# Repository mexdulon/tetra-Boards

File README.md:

View this project on [CADLAB.io](https://cadlab.io/node/872). 

# tetra-Boards
## mexdulon Modules for Experiments with Digital Electronics

This repository includes material like schematics, layouts, instructions and explanations for mexdulon tetra-Boards. 
The modular system is developed for understanding digital electronics by experimenting. Next to the standard digital components (gates, counter, register, etc.) we created also boards for analog signals and external outputs (motor driver, relay, power FET). All these published boards are licenced as Open Hardware, see below.
If you have any suggestions, modifications or extensions, please feel free to share it with us.

## List with all boards

|Code|Description                       |
|----|----------------------------------|
|7SD |7-Segment Display                 |
|ADA |Adapter 2x5 Port                  |
|ADC |Analog Digital Converter          |
|ADD |Adder 2x4 Bit                     |
|ALU |Arithmetic Logic Unit             |
|AMU |Analog Multiplexer 2x4:1          |
|AND |AND & NAND 4x2:1                  |
|ANS |Arduino Nano Shield with Display  |
|ARD |Arduino Shield (Uno, Leonardo)    |
|B7D |BCD 7-Segment Decoder             |
|BCC |BCD Up/Down Counter               |
|BNC |Binary Up/Down Counter 4 Bit      |
|BTN |Quad Buttons                      |
|C12 |Counter 12bit                     |
|CDL |Counter Divider Logic             |
|CLK |Clock Generator                   |
|CMP |Comparator 2x4 Bit                |
|CNT |Dual Counter 4 Bit                |
|D12 |Demultiplexer 1:2                 |
|D14 |Demultiplexer 1:4                 |
|D18 |Demultiplexer 1:8                 |
|DAC |Digital Analog Converter (DAC)    |
|DEC |Decoder 1:8                       |
|DFF |Dual D Flip-flop                  |
|DIP |DIP Socket                        |
|DMD |Dot Matrix Display 4x4            |
|DMX |Diode Matrix 4x4                  |
|ENC |Encoder 8:3                       | 
|FET |Quad Power FET                    |   
|INV |Dual Inverter (NOT)               |     
|IOP |Dual IO Port                      | 
|JAD |Jumper Adapter                    |   
|JKF |JK Flip-flop 2x                   |    
|JMP |Jumper 2x4                        |
|JOY |Joystick with Button              |
|KEY |Keyboard 4x4                      | 
|LAD |Line Adapter                      | 
|LED |Dual LED Display                  |
|M81 |Multiplexer 8:1                   |
|MTR |Dual Motor Shield                 |
|MUX |Multiplexer 2:1                   |
|MXC |Modulo X Counter (3/6/9/12)       | 
|N33 |Tripple NAND 3:1                  |
|NOR |OR & NOR 4x2:1                    |
|OPA |Operational Amplifier             |
|PAN |Dual Port AND 4:1                 |
|PIN |Pin Header                        |
|POR |Dual Port OR 4:1                  |
|PRG |Pseudo Random Generator           |
|PWM |PWM Generator                     |
|PXO |Dual Port XOR 4:1                 |
|QRS |Quad RS Buttons                   |
|REG |Register 2x4                      |
|RGB |RGB LED & Buzzer                  |
|RGF |Register File 4x4                 |
|RLY |Quad Relay                        |
|ROM |ROM Diodes 4x4                    |
|RSG |RS Generator                      |
|SAD |Shift Adapter                     |
|SOC |Quad Socket                       |
|SRC |SRAM Cell                         |
|SRG |Shift Register                    |
|SWG |Square Wave Generator             |
|SWI |Quad Switch                       |
|TMP |Temperature Sensor                |
|UNI |Universal Register                |
|WNG |White Noise Generator             |
|XOR |XOR & XNOR 4x2:1                  |

# Copyright and License
Copyright Oliver Krebs 2017.

This documentation describes Open Hardware and is licensed under the CERN OHL v. 1.2. 

You may redistribute and modify this documentation under the terms of the CERN OHL v.1.2. (http://ohwr.org/cernohl). This documentation is distributed WITHOUT ANY EXPRESS OR IMPLIED WARRANTY, INCLUDING OF MERCHANTABILITY, SATISFACTORY QUALITY AND FITNESS FOR A PARTICULAR PURPOSE. Please see the CERN OHL v.1.2 for applicable conditions

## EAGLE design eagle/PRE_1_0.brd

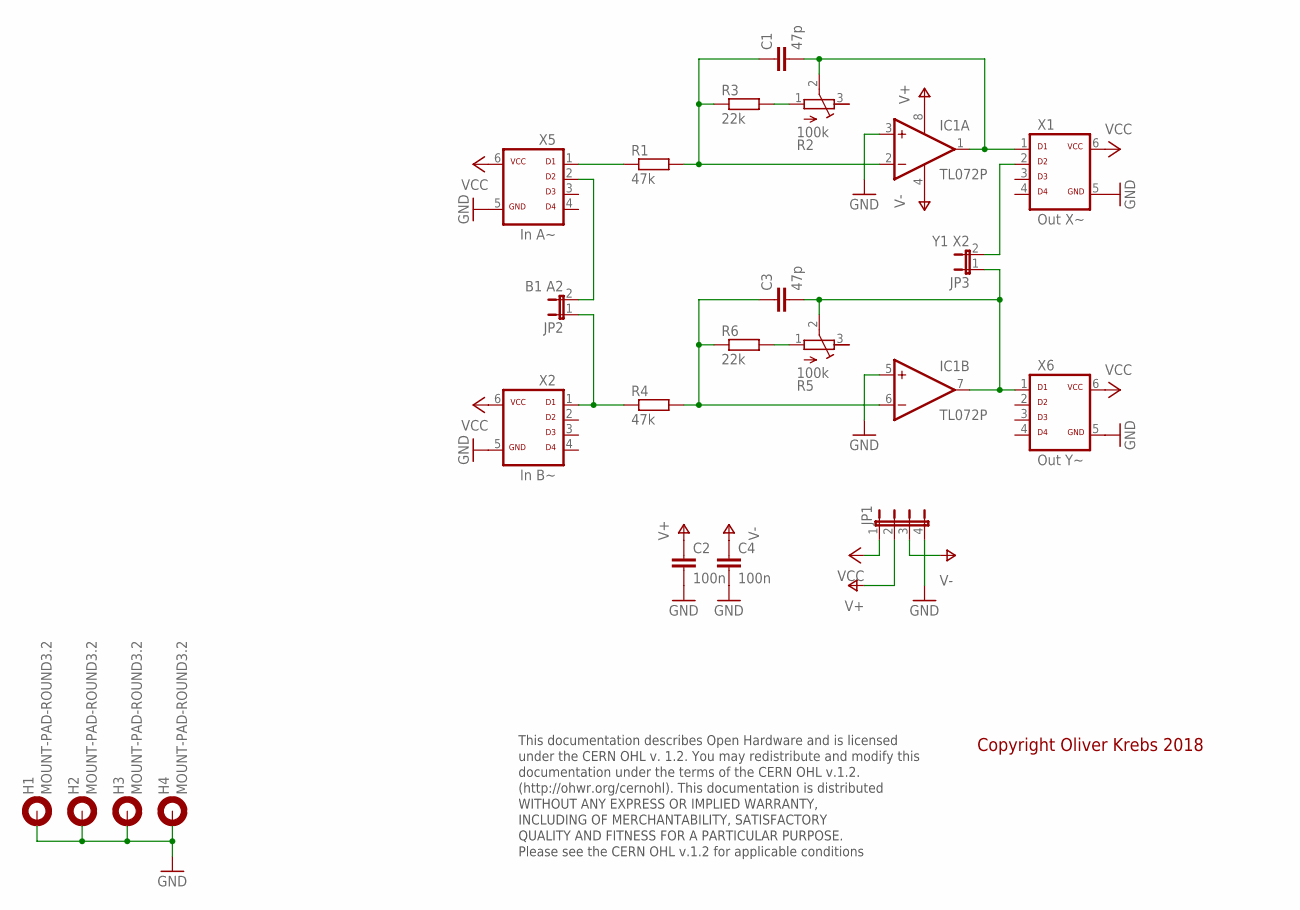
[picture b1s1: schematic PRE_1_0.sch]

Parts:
C1, C3: 47p; C050-025X075
C2, C4: 100n; C050-025X075
H1, H2, H3, H4: MOUNT-PAD-ROUND3.2; 3,2-PAD
IC1: TL072P; DIL08
JP1: JP4E; JP4
JP2: B1 A2; JP1
JP3: Y1 X2; JP1
R1, R4: 47k; 0207/10
R2, R5: 100k; ACP-6L
R3, R6: 22k; 0207/10
X1: Out X~; ML-6
X2: In B~; ML-6
X5: In A~; ML-6
X6: Out Y~; ML-6

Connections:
GND: C2.2, C4.2, H1.B3,2, H2.B3,2, H3.B3,2, H4.B3,2, IC1.3 (+IN), IC1.5 (+IN), JP1.4, X1.5, X2.5, X5.5, X6.5
unnamed: JP3.2, X1.2
unnamed: R5.1 (A), R6.2
unnamed: C1.2, IC1.1 (OUT), R2.2 (S), X1.1
unnamed: C3.2, IC1.7 (OUT), JP3.1, R5.2 (S), X6.1
unnamed: C1.1, IC1.2 (-IN), R1.2, R3.1
unnamed: JP2.2, X5.2
unnamed: R2.1 (A), R3.2
unnamed: C3.1, IC1.6 (-IN), R4.2, R6.1
unnamed: JP2.1, R4.1, X2.1
unnamed: R1.1, X5.1
V+: C2.1, IC1.8 (V+), JP1.2
V-: C4.1, IC1.4 (V-), JP1.3
VCC: JP1.1, X1.6, X2.6, X5.6, X6.6

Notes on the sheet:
This documentation describes Open Hardware and is licensed under the CERN OHL v. 1.2. You may redistribute and modify this documentation under the terms of the CERN OHL v.1.2. (http://ohwr.org/cernohl). This documentation is distributed WITHOUT ANY EXPRESS OR IMPLIED WARRANTY, INCLUDING OF MERCHANT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
Copyright Oliver Krebs 2018

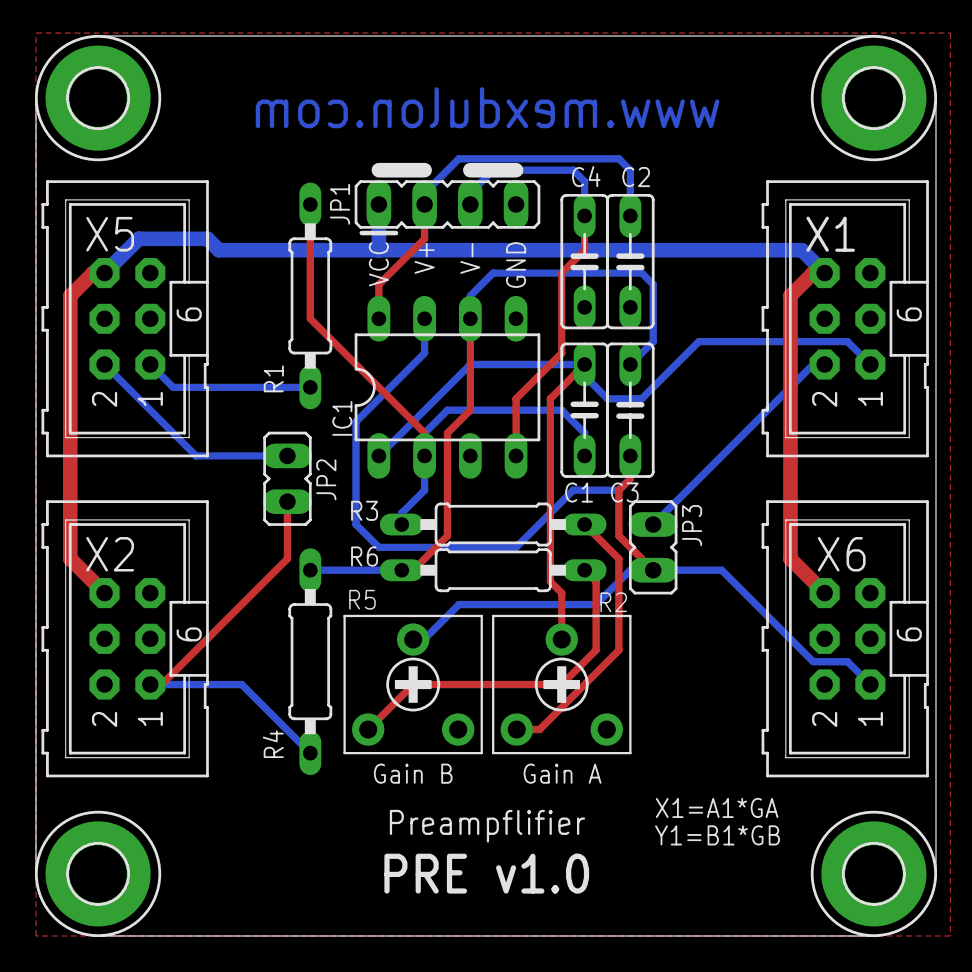
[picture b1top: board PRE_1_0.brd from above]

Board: 2 copper layers, 50.0 x 50.0 mm, 22 parts (0 on the bottom side), 14 nets.

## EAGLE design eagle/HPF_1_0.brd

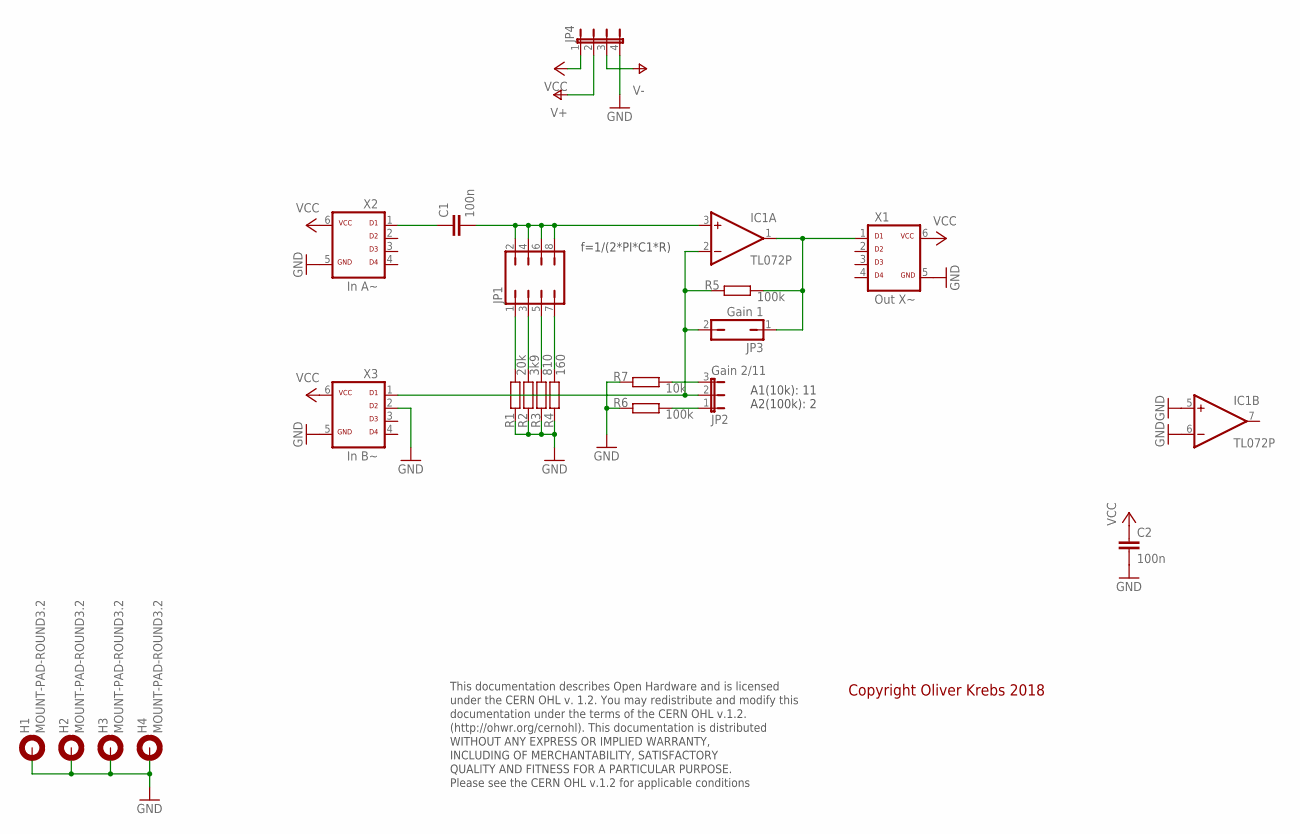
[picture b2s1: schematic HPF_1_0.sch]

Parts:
C1, C2: 100n; C050-025X075
H1, H2, H3, H4: MOUNT-PAD-ROUND3.2; 3,2-PAD
IC1: TL072P; DIL08
JP1: JP4Q
JP2: Gain 2/11; JP2-U
JP3: Gain 1; JP1
JP4: JP4E; JP4
R1: 20k; 0207/10
R2: 3k9; 0207/10
R3: 810; 0207/10
R4: 160; 0207/10
R5, R6: 100k; 0207/10
R7: 10k; 0207/10
X1: Out X~; ML-6
X2: In A~; ML-6
X3: In B~; ML-6

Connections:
GND: C2.2, H1.B3,2, H2.B3,2, H3.B3,2, H4.B3,2, IC1.5 (+IN), IC1.6 (-IN), JP4.4, R1.1, R2.1, R3.1, R4.1, R6.1, R7.1, X1.5, X2.5, X3.2, X3.5
unnamed: JP1.1, R1.2
unnamed: JP1.3, R2.2
unnamed: JP1.5, R3.2
unnamed: JP1.7, R4.2
unnamed: IC1.2 (-IN), JP2.2, JP3.2, R5.1, X3.1
unnamed: C1.2, IC1.3 (+IN), JP1.2, JP1.4, JP1.6, JP1.8
unnamed: C1.1, X2.1
unnamed: IC1.1 (OUT), JP3.1, R5.2, X1.1
unnamed: JP2.3, R7.2
unnamed: JP2.1, R6.2
V+: IC1.8 (V+), JP4.2
V-: IC1.4 (V-), JP4.3
VCC: C2.1, JP4.1, X1.6, X2.6, X3.6

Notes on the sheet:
This documentation describes Open Hardware and is licensed under the CERN OHL v. 1.2. You may redistribute and modify this documentation under the terms of the CERN OHL v.1.2. (http://ohwr.org/cernohl). This documentation is distributed WITHOUT ANY EXPRESS OR IMPLIED WARRANTY, INCLUDING OF MERCHANT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
Copyright Oliver Krebs 2018
A1(10k): 11 A2(100k): 2
f=1/(2*PI*C1*R)

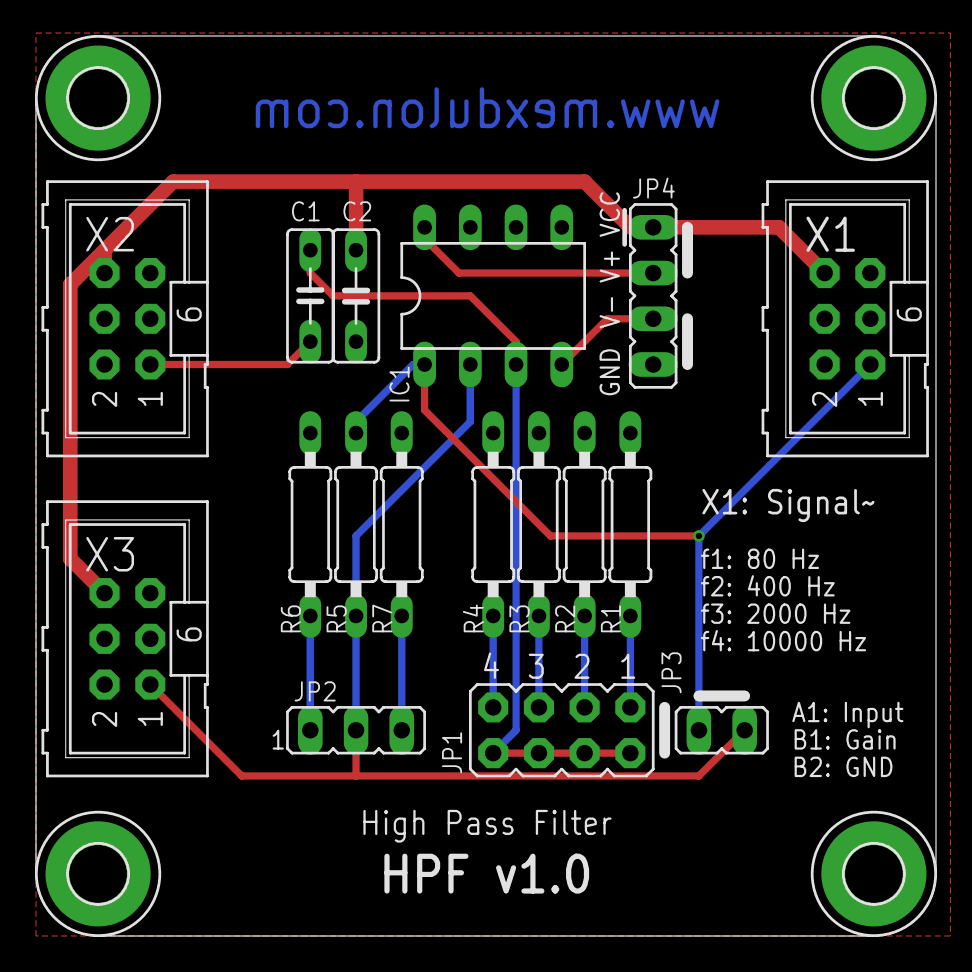
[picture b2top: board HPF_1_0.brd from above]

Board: 2 copper layers, 50.0 x 50.0 mm, 21 parts (0 on the bottom side), 14 nets.

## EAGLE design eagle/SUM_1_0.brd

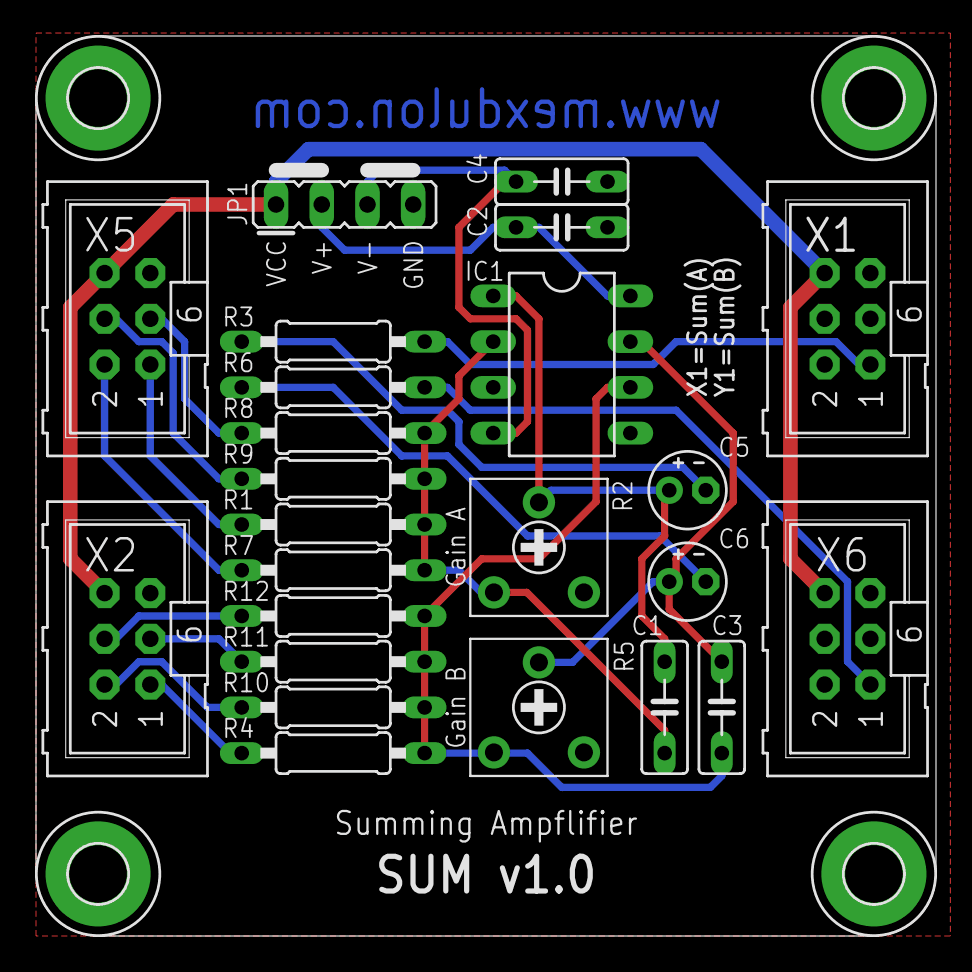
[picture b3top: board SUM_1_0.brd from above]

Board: 2 copper layers, 50.0 x 50.0 mm, 28 parts (0 on the bottom side), 20 nets.

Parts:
C1, C3: 22p; C050-025X075
C2, C4: 100n; C050-025X075
C5, C6: 4u7; E2-4
H1, H2, H3, H4: MOUNT-PAD-ROUND3.2; 3,2-PAD
IC1: TL072P; DIL08
JP1: JP4
R1, R4, R7, R8, R9, R10, R11, R12: 22k; 0207/10
R2, R5: 25k; ACP-6L
R3, R6: 47; 0207/10
X1: X~; ML-6
X2: B~; ML-6
X5: A~; ML-6
X6: Y~; ML-6

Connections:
GND: C2.2, C4.2, H1.B3,2, H2.B3,2, H3.B3,2, H4.B3,2, IC1.3, IC1.5, JP1.4, X1.5, X2.5, X5.5, X6.5
unnamed: C5.-, R3.1
unnamed: R3.2, X1.1
unnamed: C1.2, C5.+, IC1.1, R2.2
unnamed: C3.2, C6.+, IC1.7, R5.2
unnamed: C1.1, IC1.2, R1.2, R2.1, R7.2, R8.2, R9.2
unnamed: R7.1, X5.2
unnamed: C3.1, IC1.6, R4.2, R5.1, R10.2, R11.2, R12.2
unnamed: C6.-, R6.1
unnamed: R4.1, X2.1
unnamed: R1.1, X5.1
unnamed: R8.1, X5.3
unnamed: R9.1, X5.4
unnamed: R6.2, X6.1
unnamed: R10.1, X2.2
unnamed: R11.1, X2.3
unnamed: R12.1, X2.4
V+: C2.1, IC1.8, JP1.2
V-: C4.1, IC1.4, JP1.3
VCC: JP1.1, X1.6, X2.6, X5.6, X6.6

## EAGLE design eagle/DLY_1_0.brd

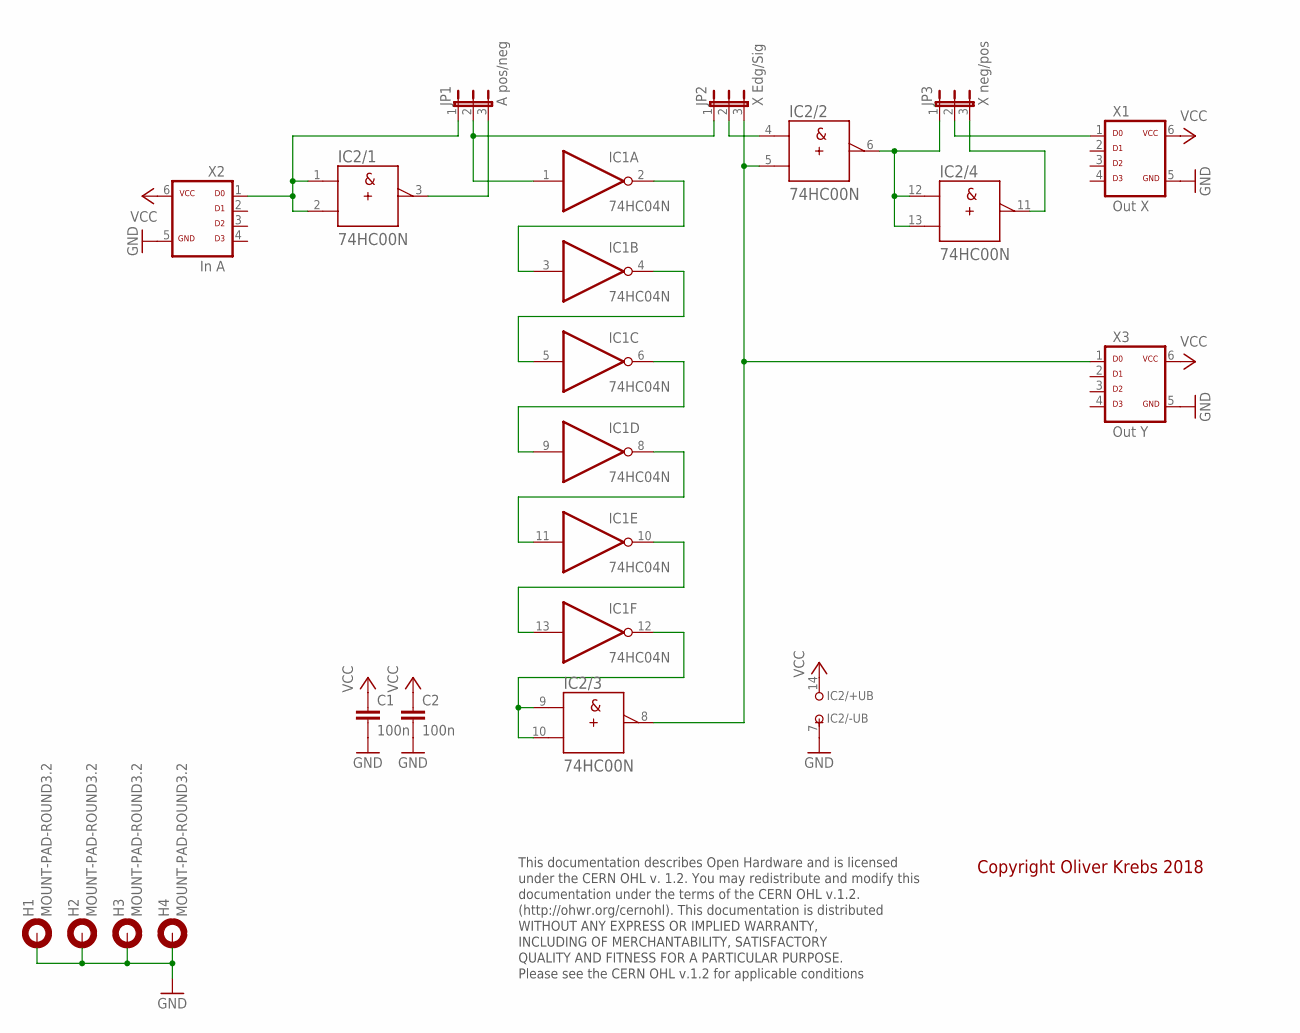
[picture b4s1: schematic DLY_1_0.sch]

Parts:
C1, C2: 100n; C050-025X075
H1, H2, H3, H4: MOUNT-PAD-ROUND3.2; 3,2-PAD
IC1: 74HC04N; DIL14
IC2: 74HC00N; DIL14
JP1: A pos/neg; JP2
JP2: X Edg/Sig; JP2
JP3: X neg/pos; JP2
X1: Out X; ML-6
X2: In A; ML-6
X3: Out Y; ML-6

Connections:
GND: C1.2, C2.2, H1.B3,2, H2.B3,2, H3.B3,2, H4.B3,2, IC1.7 (GND), IC2.7 (-UB), X1.5, X2.5, X3.5
unnamed: IC2.1 (A), IC2.2 (B), JP1.1, X2.1
unnamed: IC1.2 (O), IC1.3 (I)
unnamed: IC1.4 (O), IC1.5 (I)
unnamed: IC1.6 (O), IC1.9 (I)
unnamed: IC1.8 (O), IC1.11 (I)
unnamed: IC2.5 (B), IC2.8 (Y), JP2.3, X3.1
unnamed: IC2.3 (Y), JP1.3
unnamed: IC1.1 (I), JP1.2, JP2.1
unnamed: IC2.4 (A), JP2.2
unnamed: IC1.12 (O), IC2.9 (A), IC2.10 (B)
unnamed: IC2.6 (Y), IC2.12 (A), IC2.13 (B), JP3.1
unnamed: IC2.11 (Y), JP3.3
unnamed: JP3.2, X1.1
unnamed: IC1.10 (O), IC1.13 (I)
VCC: C1.1, C2.1, IC1.14 (VCC), IC2.14 (+UB), X1.6, X2.6, X3.6

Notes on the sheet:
This documentation describes Open Hardware and is licensed under the CERN OHL v. 1.2. You may redistribute and modify this documentation under the terms of the CERN OHL v.1.2. (http://ohwr.org/cernohl). This documentation is distributed WITHOUT ANY EXPRESS OR IMPLIED WARRANTY, INCLUDING OF MERCHANT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
Copyright Oliver Krebs 2018

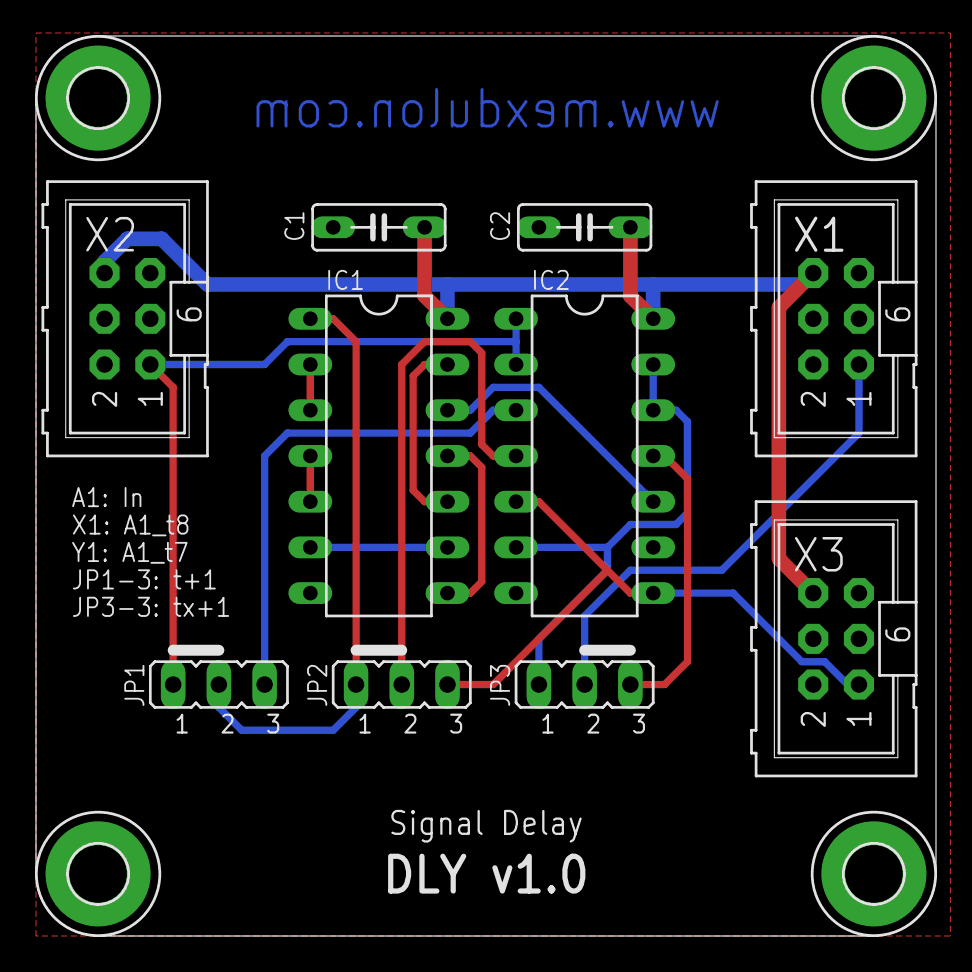
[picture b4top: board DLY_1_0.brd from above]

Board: 2 copper layers, 50.0 x 50.0 mm, 14 parts (0 on the bottom side), 16 nets.

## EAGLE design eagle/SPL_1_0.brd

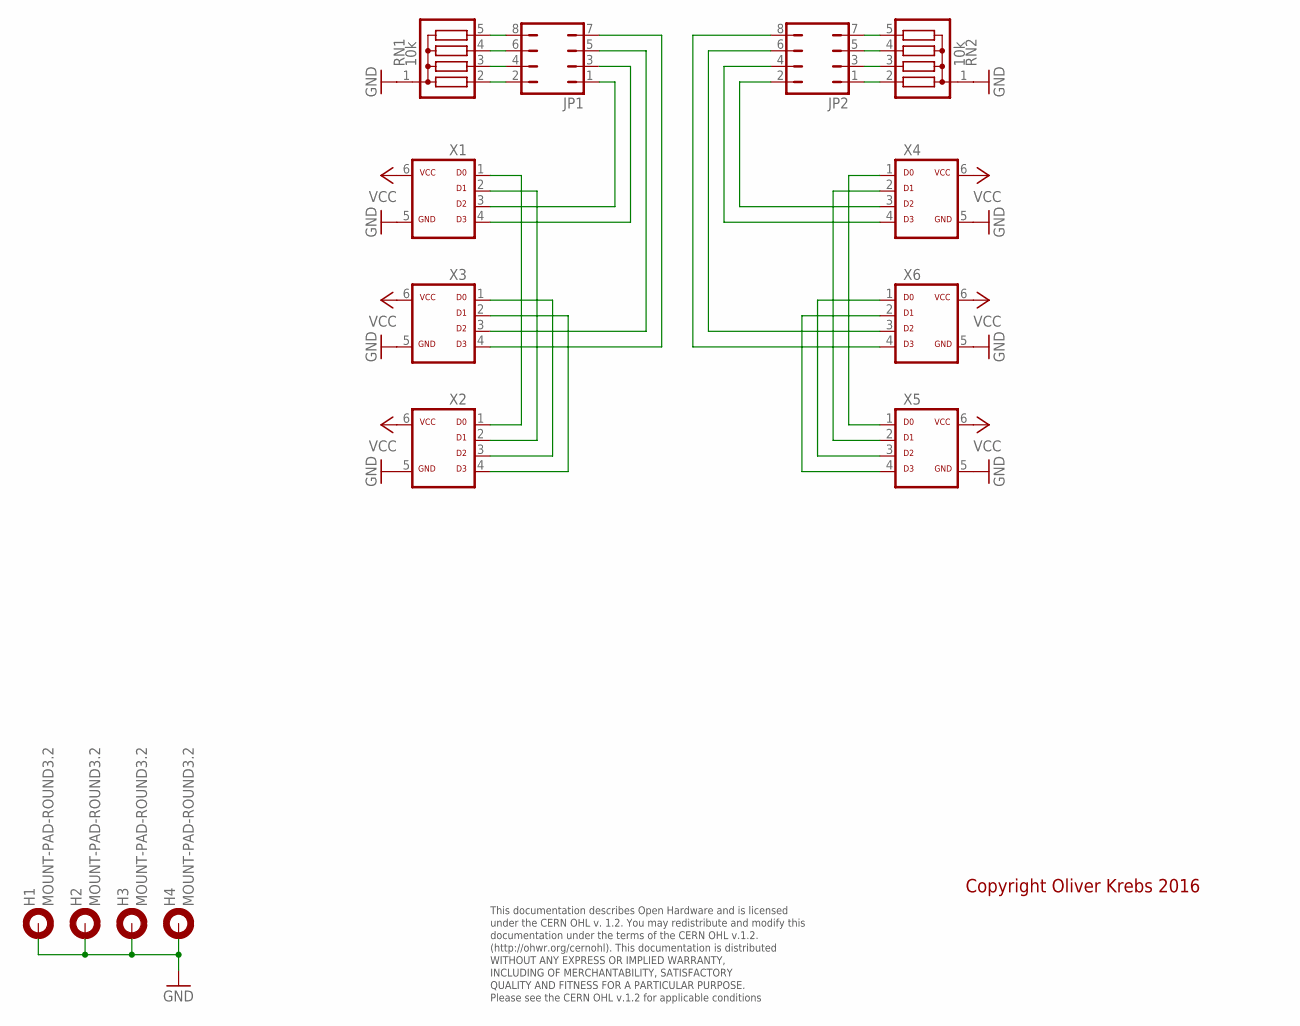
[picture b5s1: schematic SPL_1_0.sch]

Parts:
H1, H2, H3, H4: MOUNT-PAD-ROUND3.2; 3,2-PAD
JP1, JP2: JP4Q
RN1, RN2: 10k; SIL5
X1, X2, X3, X4, X5, X6: ML6D; ML-6

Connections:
GND: H1.B3,2, H2.B3,2, H3.B3,2, H4.B3,2, RN1.1, RN2.1, X1.5, X2.5, X3.5, X4.5, X5.5, X6.5
unnamed: X1.1, X2.1
unnamed: X1.2, X2.2
unnamed: X2.3, X3.1
unnamed: X2.4, X3.2
unnamed: X4.1, X5.1
unnamed: X4.2, X5.2
unnamed: X5.3, X6.1
unnamed: X5.4, X6.2
unnamed: JP1.2, RN1.2
unnamed: JP1.4, RN1.3
unnamed: JP1.6, RN1.4
unnamed: JP1.8, RN1.5
unnamed: JP2.1, RN2.2
unnamed: JP2.3, RN2.3
unnamed: JP2.5, RN2.4
unnamed: JP2.7, RN2.5
unnamed: JP1.1, X1.3
unnamed: JP1.3, X1.4
unnamed: JP1.5, X3.3
unnamed: JP1.7, X3.4
unnamed: JP2.8, X6.4
unnamed: JP2.6, X6.3
unnamed: JP2.4, X4.4
unnamed: JP2.2, X4.3
VCC: X1.6, X2.6, X3.6, X4.6, X5.6, X6.6

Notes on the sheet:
This documentation describes Open Hardware and is licensed under the CERN OHL v. 1.2. You may redistribute and modify this documentation under the terms of the CERN OHL v.1.2. (http://ohwr.org/cernohl). This documentation is distributed WITHOUT ANY EXPRESS OR IMPLIED WARRANTY, INCLUDING OF MERCHANT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
Copyright Oliver Krebs 2016

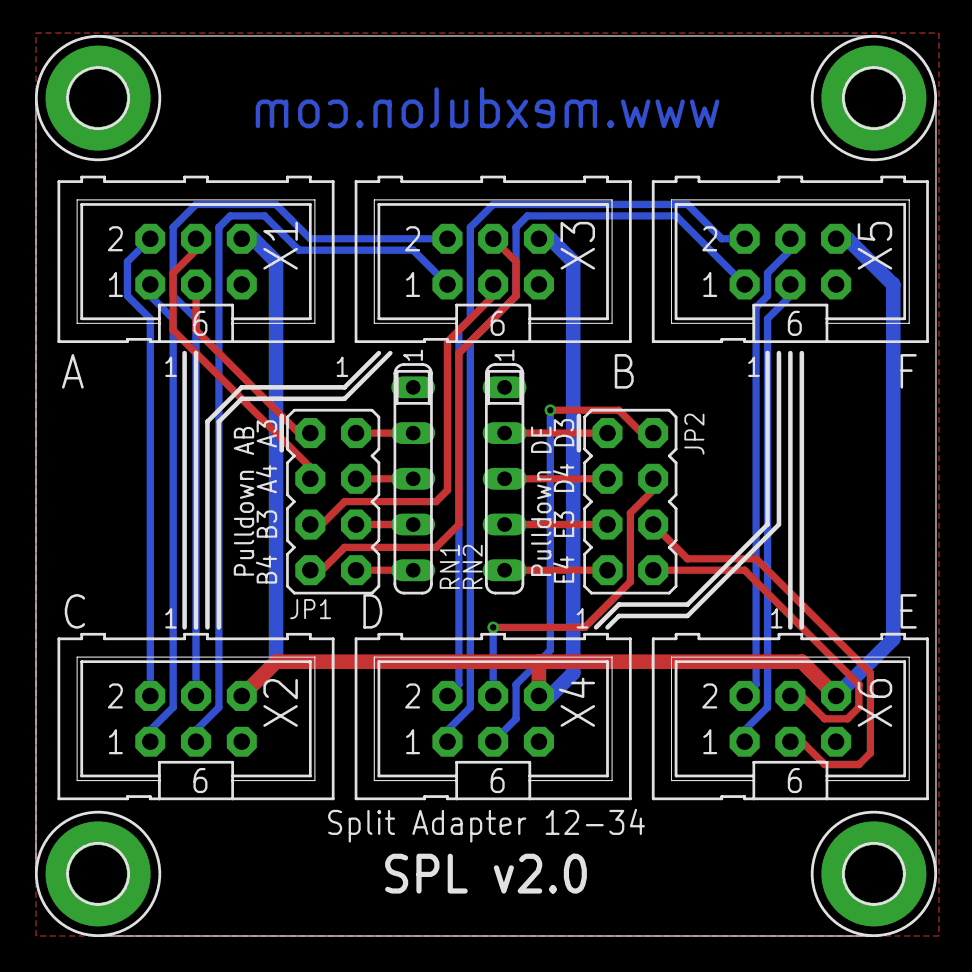
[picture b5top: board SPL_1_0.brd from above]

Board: 2 copper layers, 50.0 x 50.0 mm, 14 parts (0 on the bottom side), 26 nets.

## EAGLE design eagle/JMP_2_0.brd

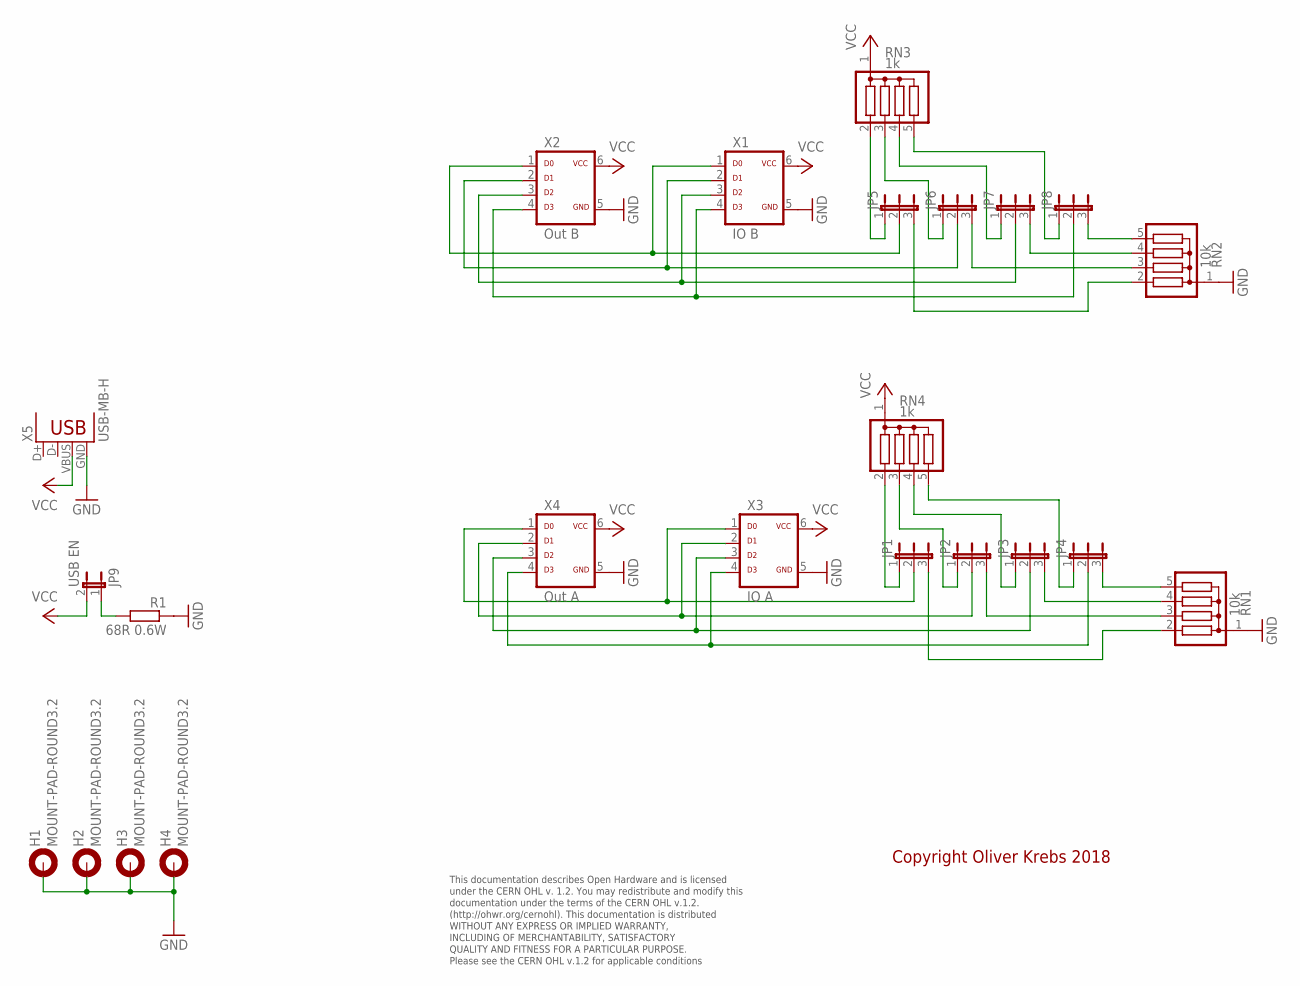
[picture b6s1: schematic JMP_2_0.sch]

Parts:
H1, H2, H3, H4: MOUNT-PAD-ROUND3.2; 3,2-PAD
JP1, JP2, JP3, JP4, JP5, JP6, JP7, JP8: JP2E; JP2-S
JP9: USB EN; JP1
R1: 68R 0.6W; 0207/10
RN1, RN2: 10k; SIL5
RN3, RN4: 1k; SIL5
X1: IO B; ML-6
X2: Out B; ML-6
X3: IO A; ML-6
X4: Out A; ML-6
X5: USB-MB-H

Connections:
GND: H1.B3,2, H2.B3,2, H3.B3,2, H4.B3,2, R1.1, RN1.1, RN2.1, X1.5, X2.5, X3.5, X4.5, X5.GND
unnamed: JP5.2, X1.1, X2.1
unnamed: JP6.2, X1.2, X2.2
unnamed: JP1.2, X3.1, X4.1
unnamed: JP8.2, X1.4, X2.4
unnamed: JP2.2, X3.2, X4.2
unnamed: JP4.2, X3.4, X4.4
unnamed: JP7.2, X1.3, X2.3
unnamed: JP3.2, X3.3, X4.3
unnamed: JP8.1, RN3.5
unnamed: JP9.1, R1.2
unnamed: JP5.1, RN3.2
unnamed: JP6.1, RN3.3
unnamed: JP7.1, RN3.4
unnamed: JP1.1, RN4.2
unnamed: JP2.1, RN4.3
unnamed: JP3.1, RN4.4
unnamed: JP4.1, RN4.5
unnamed: JP5.3, RN2.2
unnamed: JP6.3, RN2.3
unnamed: JP7.3, RN2.4
unnamed: JP8.3, RN2.5
unnamed: JP4.3, RN1.5
unnamed: JP3.3, RN1.4
unnamed: JP2.3, RN1.3
unnamed: JP1.3, RN1.2
VCC: JP9.2, RN3.1, RN4.1, X1.6, X2.6, X3.6, X4.6, X5.VBUS

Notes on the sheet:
This documentation describes Open Hardware and is licensed under the CERN OHL v. 1.2. You may redistribute and modify this documentation under the terms of the CERN OHL v.1.2. (http://ohwr.org/cernohl). This documentation is distributed WITHOUT ANY EXPRESS OR IMPLIED WARRANTY, INCLUDING OF MERCHANT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
Copyright Oliver Krebs 2018

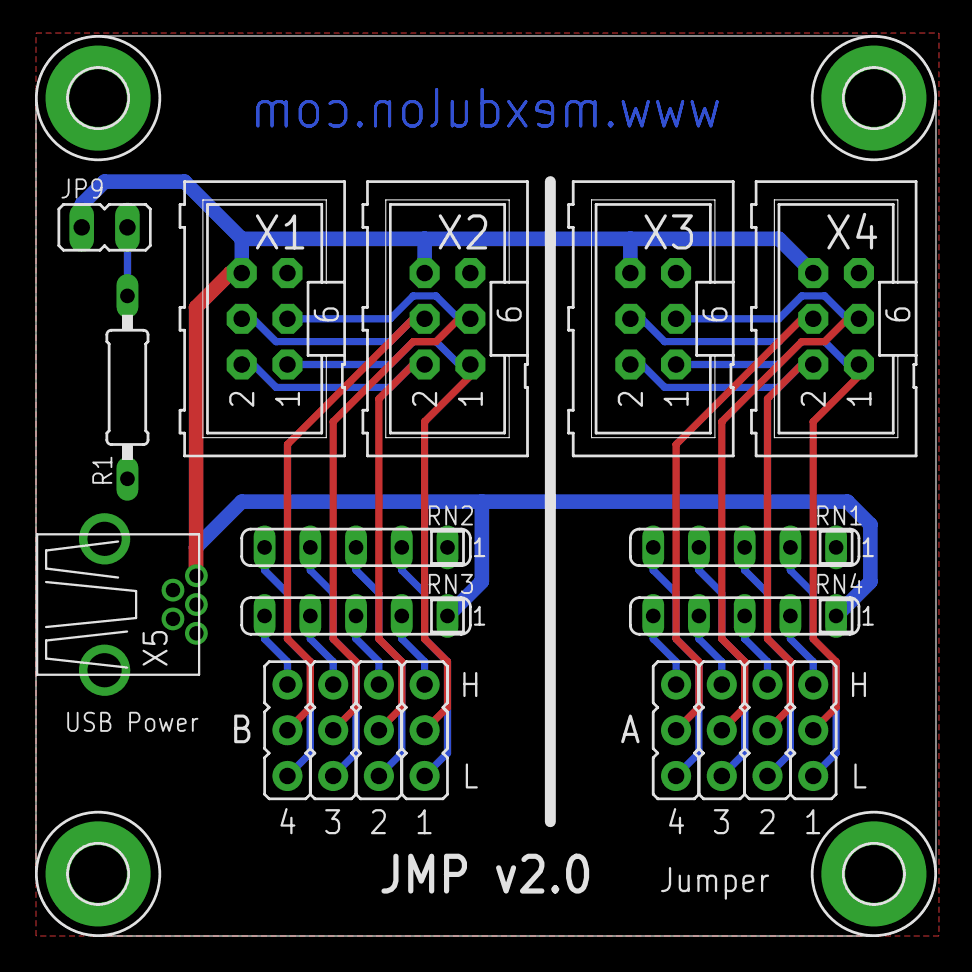
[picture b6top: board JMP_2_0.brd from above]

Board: 2 copper layers, 50.0 x 50.0 mm, 23 parts (0 on the bottom side), 27 nets.

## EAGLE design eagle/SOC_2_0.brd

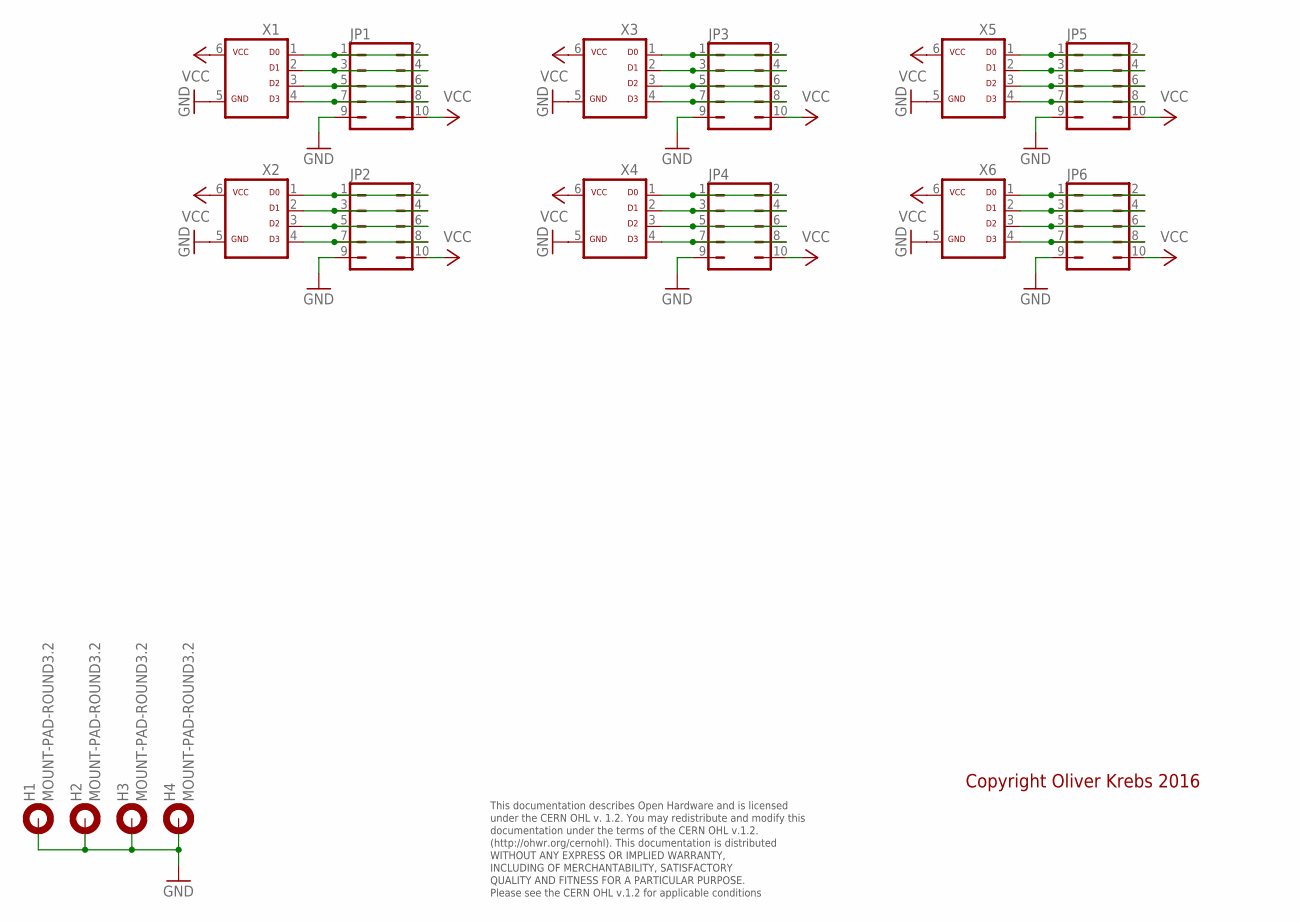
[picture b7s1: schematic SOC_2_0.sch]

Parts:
H1, H2, H3, H4: MOUNT-PAD-ROUND3.2; 3,2-PAD
JP1, JP2, JP3, JP4, JP5, JP6: JP5Q
X1, X2, X3, X4, X5, X6: ML6D; ML-6

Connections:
GND: H1.B3,2, H2.B3,2, H3.B3,2, H4.B3,2, JP1.9, JP2.9, JP3.9, JP4.9, JP5.9, JP6.9, X1.5, X2.5, X3.5, X4.5, X5.5, X6.5
unnamed: JP1.1, JP1.2, X1.1
unnamed: JP1.3, JP1.4, X1.2
unnamed: JP1.5, JP1.6, X1.3
unnamed: JP1.7, JP1.8, X1.4
unnamed: JP2.1, JP2.2, X2.1
unnamed: JP2.3, JP2.4, X2.2
unnamed: JP2.5, JP2.6, X2.3
unnamed: JP2.7, JP2.8, X2.4
unnamed: JP3.1, JP3.2, X3.1
unnamed: JP3.3, JP3.4, X3.2
unnamed: JP3.5, JP3.6, X3.3
unnamed: JP3.7, JP3.8, X3.4
unnamed: JP4.1, JP4.2, X4.1
unnamed: JP4.3, JP4.4, X4.2
unnamed: JP4.5, JP4.6, X4.3
unnamed: JP4.7, JP4.8, X4.4
unnamed: JP5.1, JP5.2, X5.1
unnamed: JP5.3, JP5.4, X5.2
unnamed: JP5.5, JP5.6, X5.3
unnamed: JP5.7, JP5.8, X5.4
unnamed: JP6.1, JP6.2, X6.1
unnamed: JP6.3, JP6.4, X6.2
unnamed: JP6.5, JP6.6, X6.3
unnamed: JP6.7, JP6.8, X6.4
VCC: JP1.10, JP2.10, JP3.10, JP4.10, JP5.10, JP6.10, X1.6, X2.6, X3.6, X4.6, X5.6, X6.6

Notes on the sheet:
This documentation describes Open Hardware and is licensed under the CERN OHL v. 1.2. You may redistribute and modify this documentation under the terms of the CERN OHL v.1.2. (http://ohwr.org/cernohl). This documentation is distributed WITHOUT ANY EXPRESS OR IMPLIED WARRANTY, INCLUDING OF MERCHANT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
Copyright Oliver Krebs 2016

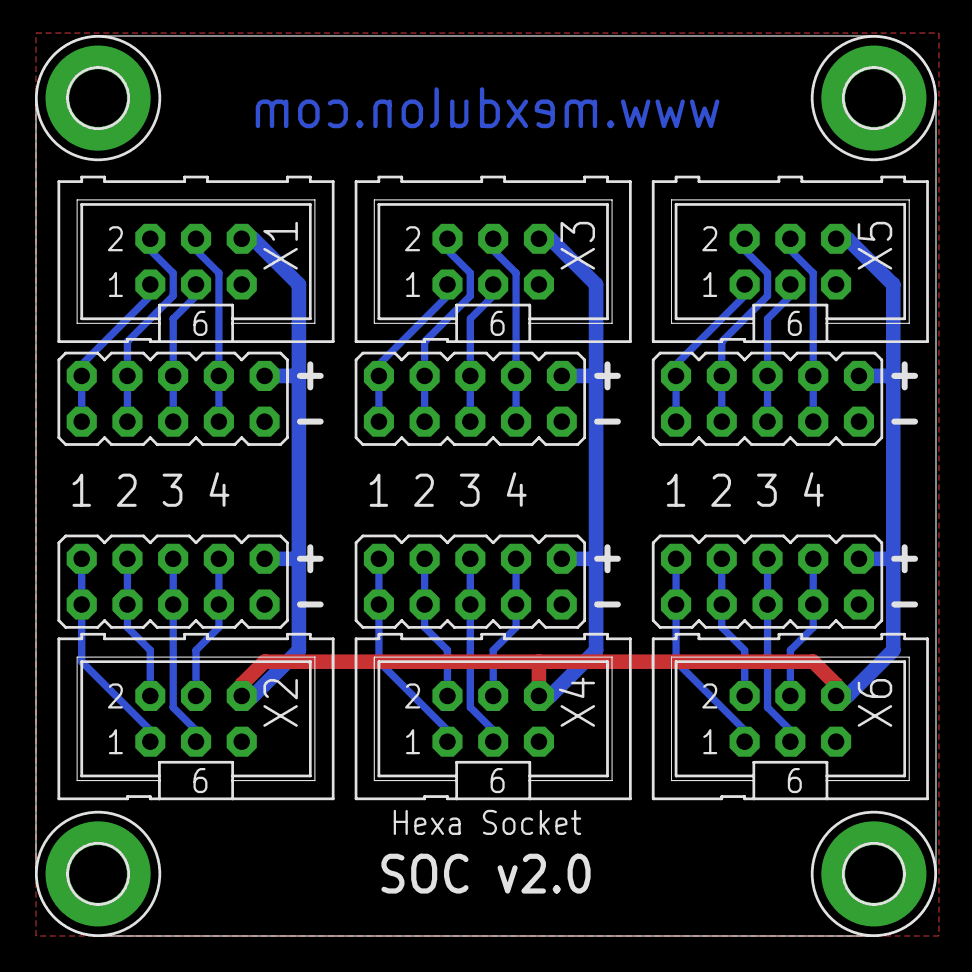
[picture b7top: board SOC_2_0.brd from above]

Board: 2 copper layers, 50.0 x 50.0 mm, 16 parts (0 on the bottom side), 26 nets.

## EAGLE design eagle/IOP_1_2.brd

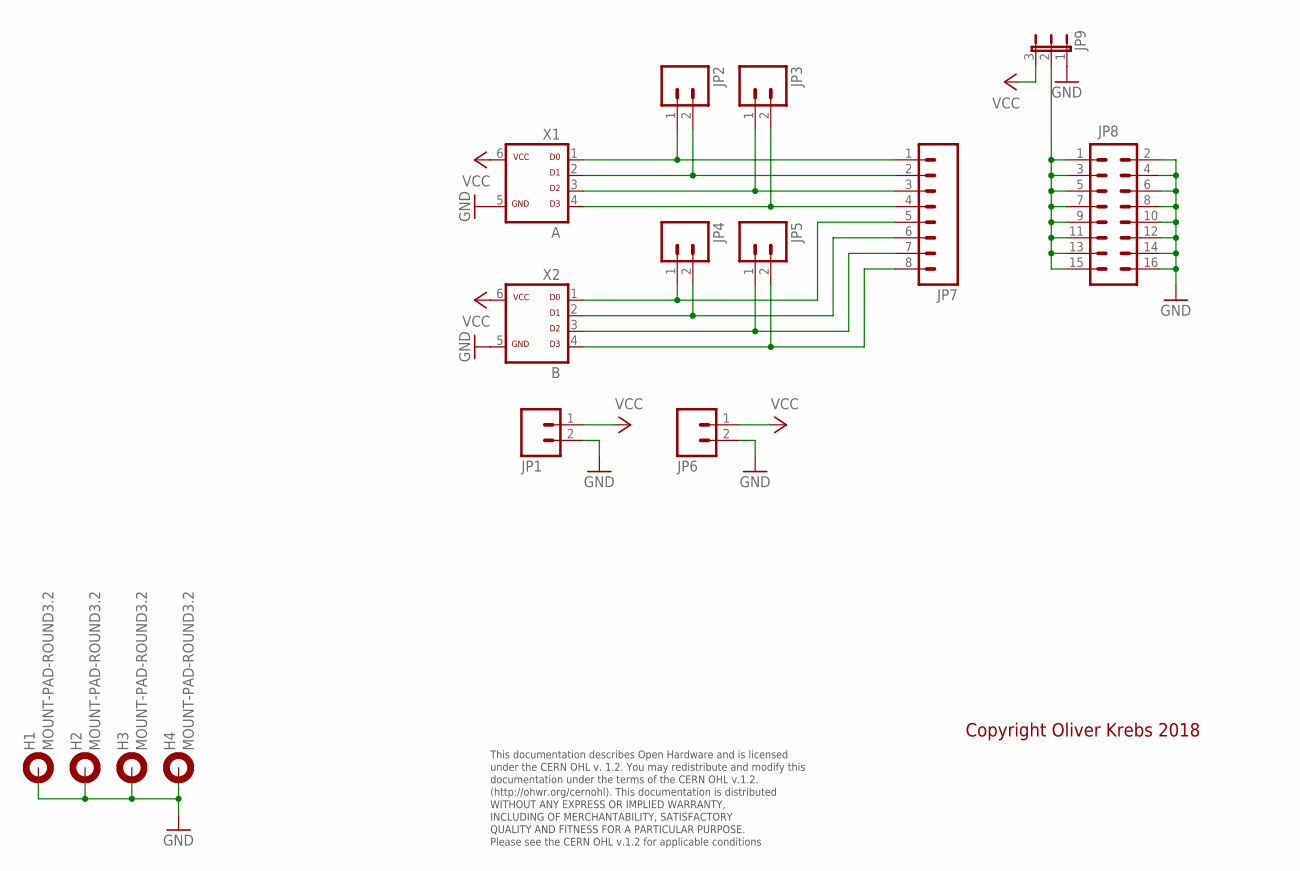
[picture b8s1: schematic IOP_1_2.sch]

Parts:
H1, H2, H3, H4: MOUNT-PAD-ROUND3.2; 3,2-PAD
JP1, JP2, JP3, JP4, JP5, JP6: M021.3MM-5.08; 1X02_BIG_5.08
JP7: M08; 1X08_ROUND
JP8: M08X2; 2X8
JP9: JP2EJP2-U; JP2-U
X1: A; ML-6
X2: B; ML-6

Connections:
GND: H1.B3,2, H2.B3,2, H3.B3,2, H4.B3,2, JP1.2, JP6.2, JP8.2, JP8.4, JP8.6, JP8.8, JP8.10, JP8.12, JP8.14, JP8.16, JP9.1, X1.5, X2.5
unnamed: JP2.2, JP7.2, X1.2
unnamed: JP2.1, JP7.1, X1.1
unnamed: JP3.1, JP7.3, X1.3
unnamed: JP3.2, JP7.4, X1.4
unnamed: JP8.1, JP8.3, JP8.5, JP8.7, JP8.9, JP8.11, JP8.13, JP8.15, JP9.2
unnamed: JP5.1, JP7.7, X2.3
unnamed: JP5.2, JP7.8, X2.4
unnamed: JP4.1, JP7.5, X2.1
unnamed: JP4.2, JP7.6, X2.2
VCC: JP1.1, JP6.1, JP9.3, X1.6, X2.6

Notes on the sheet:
This documentation describes Open Hardware and is licensed under the CERN OHL v. 1.2. You may redistribute and modify this documentation under the terms of the CERN OHL v.1.2. (http://ohwr.org/cernohl). This documentation is distributed WITHOUT ANY EXPRESS OR IMPLIED WARRANTY, INCLUDING OF MERCHANT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
Copyright Oliver Krebs 2018

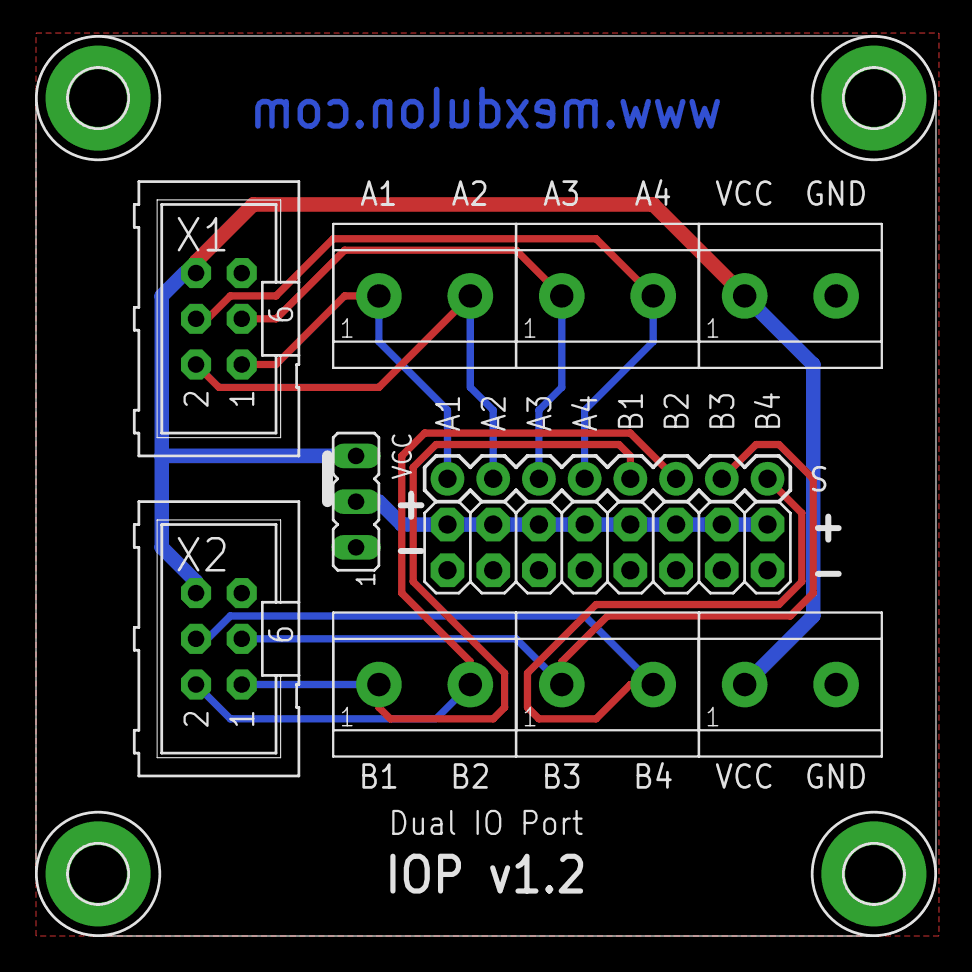
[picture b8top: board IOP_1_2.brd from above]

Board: 2 copper layers, 50.0 x 50.0 mm, 15 parts (0 on the bottom side), 11 nets.

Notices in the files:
eagle/DLY_1_0.brd:
Licensed under CERN OHL v.1.2
parts and their libraries:
SparkFun-Connectors: Licensing: Creative Commons ShareAlike 4.0 International - https://creativecommons.org/licenses/by-sa/4.0
